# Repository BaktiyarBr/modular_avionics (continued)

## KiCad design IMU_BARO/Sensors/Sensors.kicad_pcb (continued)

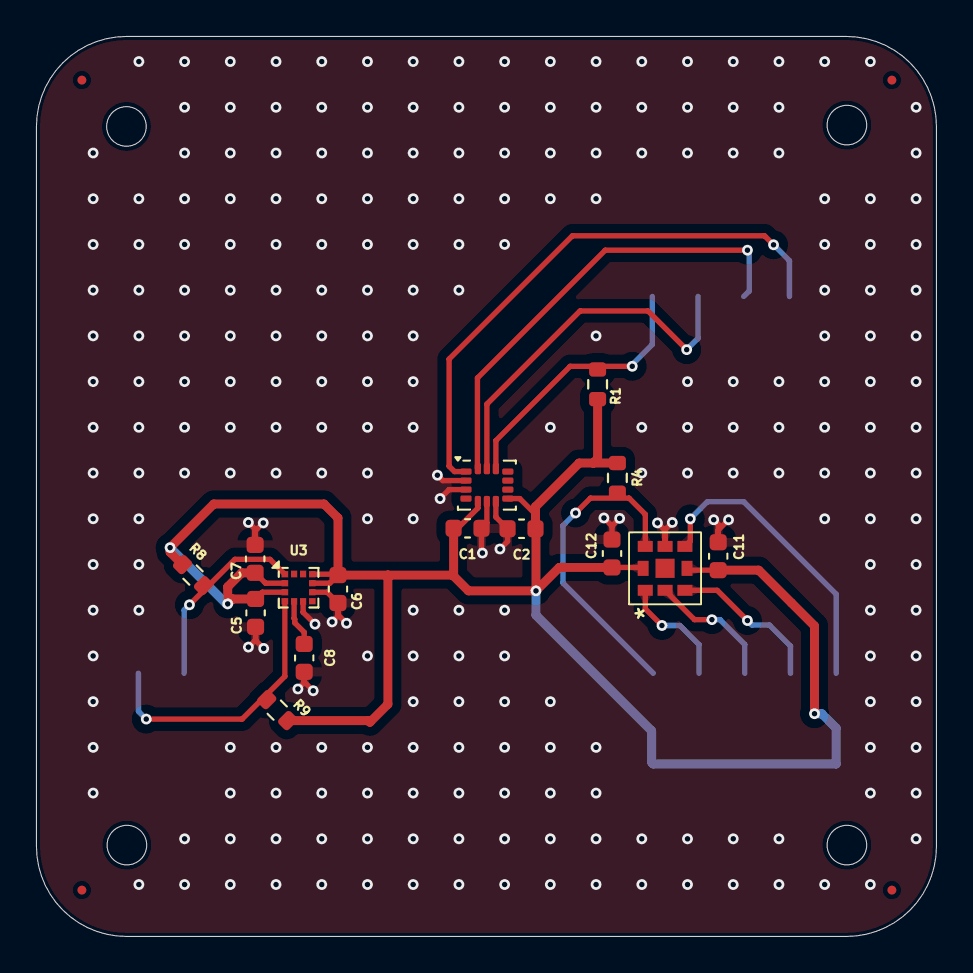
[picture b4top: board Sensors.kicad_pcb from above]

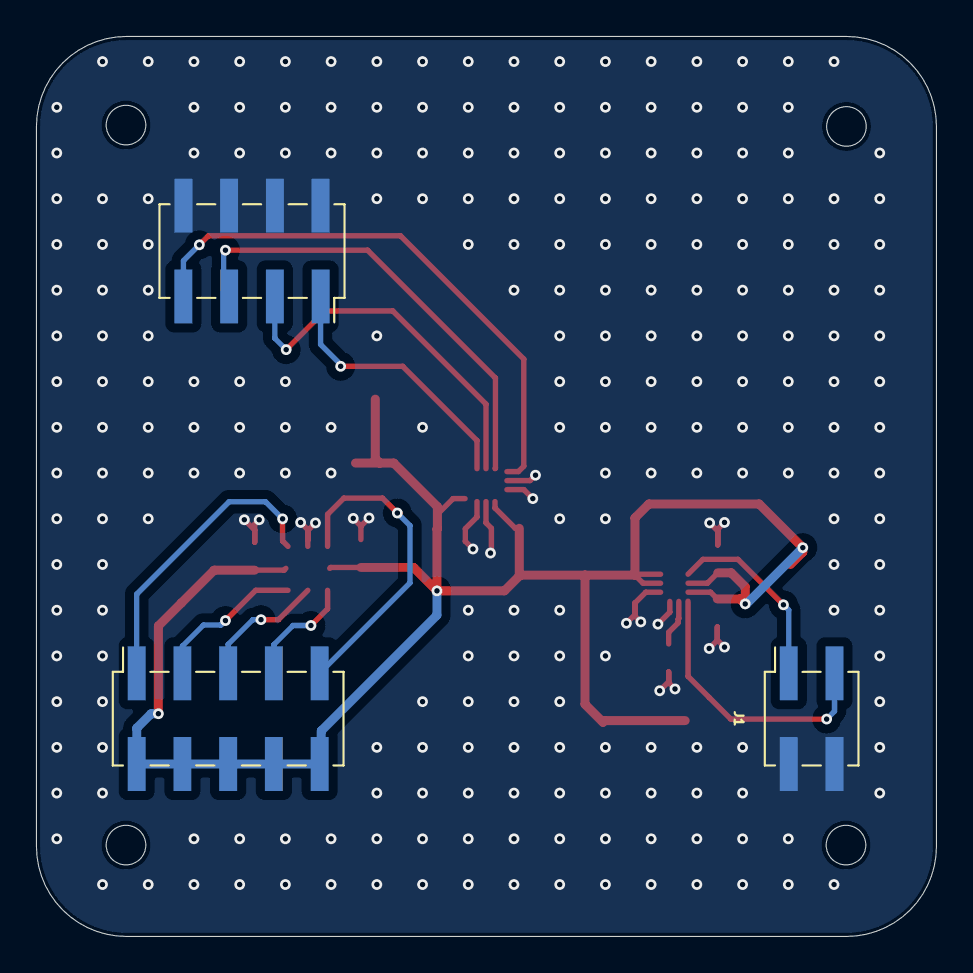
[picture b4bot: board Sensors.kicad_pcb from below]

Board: 2 copper layers, 50.0 x 50.0 mm, 26 parts (3 on the bottom side), 14 nets.

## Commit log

2025-02-12 Auto commit: 2025-02-12_10-25
2025-02-17 Auto commit: 2025-02-17_10-53
2025-02-26 Auto commit: 2025-02-26_20-32
2025-02-27 Auto commit: 2025-02-27_10-15
2025-03-27 Auto commit: 2025-03-27_15-05
